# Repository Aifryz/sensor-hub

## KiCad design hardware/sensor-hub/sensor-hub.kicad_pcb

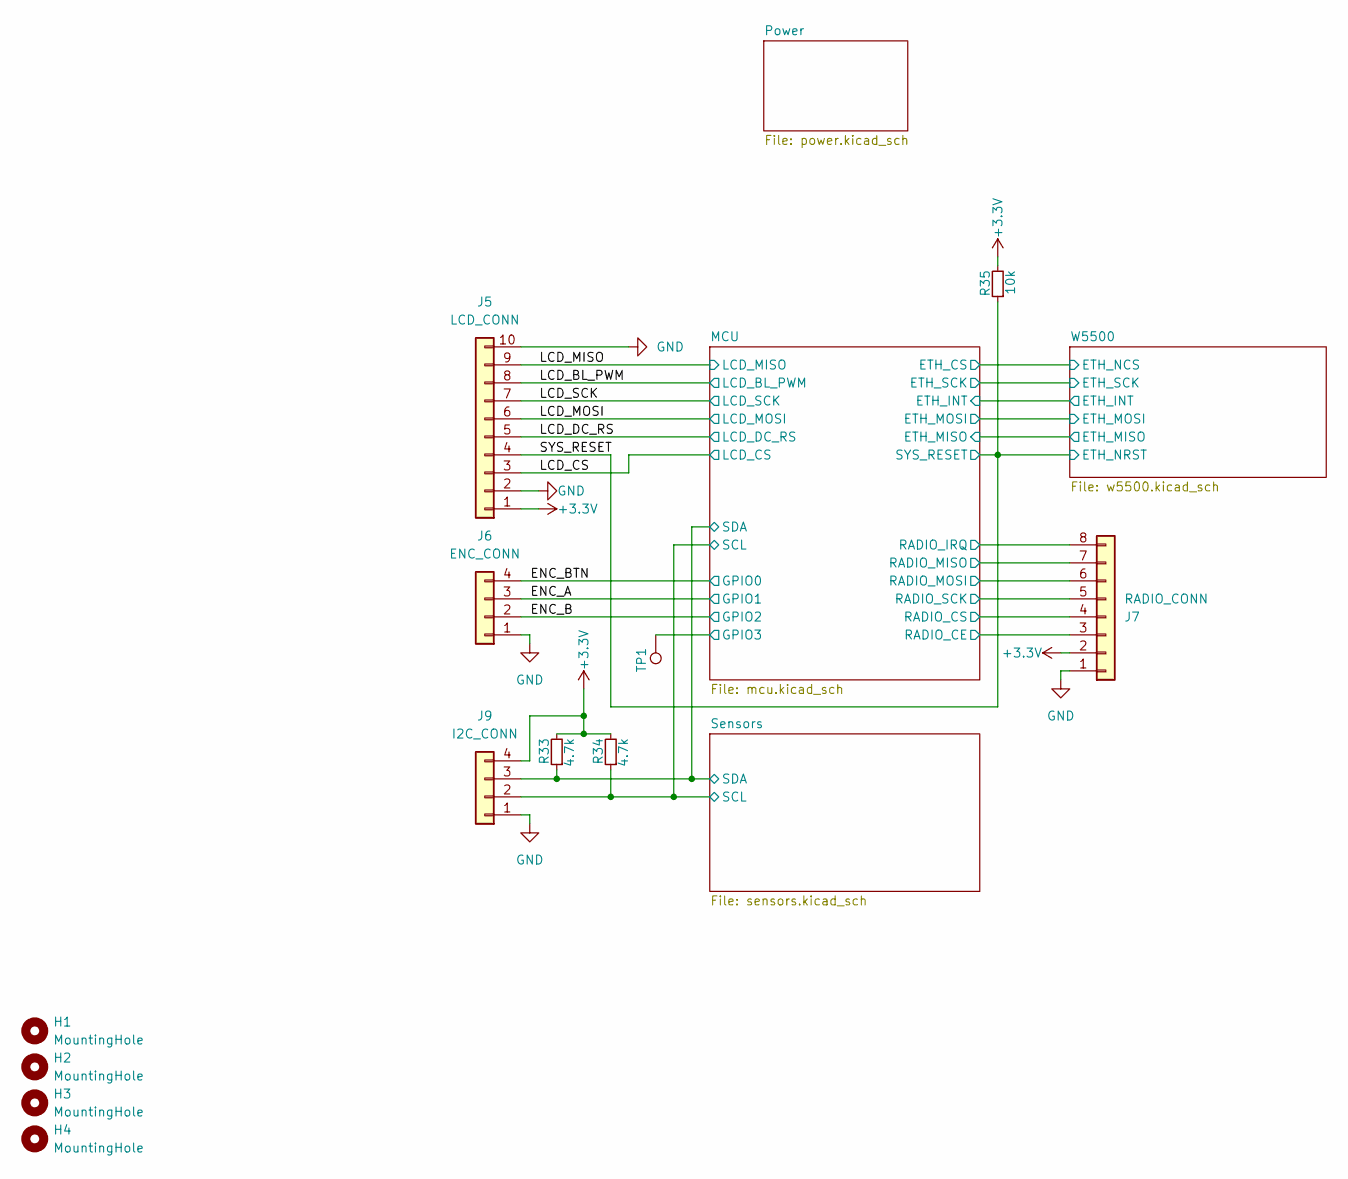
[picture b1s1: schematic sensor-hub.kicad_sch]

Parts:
H1, H2, H3, H4: MountingHole; MountingHole_3mm
J5: LCD_CONN; TE_Micro-MaTch_1-215079-0_2x05_P1.27mm_Vertical
J6: ENC_CONN; TE_Micro-MaTch_215079-4_2x02_P1.27mm_Vertical
J7: RADIO_CONN; TE_Micro-MaTch_215079-8_2x04_P1.27mm_Vertical
J9: I2C_CONN; PinHeader_1x04_P2.54mm_Vertical
R33, R34: 4.7k; R_0603_1608Metric
R35: 10k; R_0603_1608Metric
TP1: TestPoint; TestPoint_Pad_D1.0mm

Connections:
+3.3V: J5.1, J7.2, J9.4, R33.2, R34.2, R35.2; also elsewhere on the board
/ENC_A: J6.3; also elsewhere on the board
/ENC_B: J6.2; also elsewhere on the board
/ENC_BTN: J6.4; also elsewhere on the board
/LCD_BL_PWM: J5.8; also elsewhere on the board
/LCD_CS: J5.3; also elsewhere on the board
/LCD_DC_RS: J5.5; also elsewhere on the board
/LCD_MISO: J5.9; also elsewhere on the board
/LCD_MOSI: J5.6; also elsewhere on the board
/LCD_SCK: J5.7; also elsewhere on the board
/MCU/GPIO3: TP1.1; also elsewhere on the board
/MCU/RADIO_CE: J7.3; also elsewhere on the board
/MCU/RADIO_CS: J7.4; also elsewhere on the board
/MCU/RADIO_IRQ: J7.8; also elsewhere on the board
/MCU/RADIO_MISO: J7.7; also elsewhere on the board
/MCU/RADIO_MOSI: J7.6; also elsewhere on the board
/MCU/RADIO_SCK: J7.5; also elsewhere on the board
/MCU/SCL: J9.2, R34.1; also elsewhere on the board
/MCU/SDA: J9.3, R33.1; also elsewhere on the board
/SYS_RESET: J5.4, R35.1; also elsewhere on the board
GND: J5.2, J5.10, J6.1, J7.1, J9.1; also elsewhere on the board

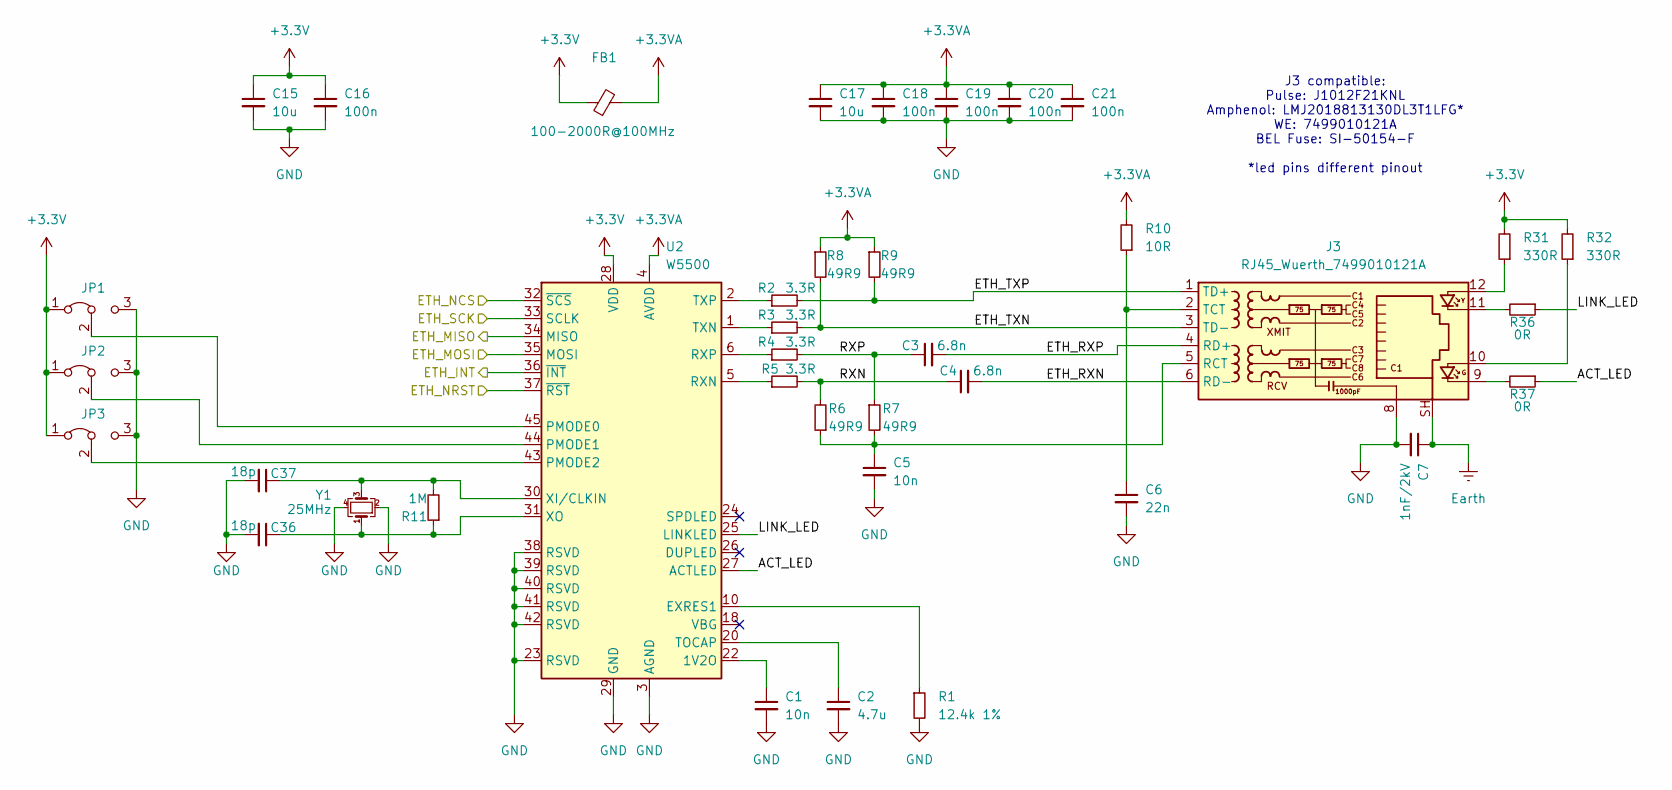
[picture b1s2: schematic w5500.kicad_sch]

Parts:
C1, C5: 10n; C_0603_1608Metric
C2: 4.7u; C_0603_1608Metric
C3, C4: 6.8n; C_0603_1608Metric
C6: 22n; C_0603_1608Metric
C7: 1nF/2kV; C_1206_3216Metric
C15, C17: 10u; C_0805_2012Metric
C16, C18, C19, C20, C21: 100n; C_0603_1608Metric
C36, C37: 18p; C_0603_1608Metric
FB1: 100-2000R@100MHz; L_0603_1608Metric
J3: RJ45_Wuerth_7499010121A; RJ45_Wuerth_7499010121A_Horizontal
JP1, JP2, JP3: SolderJumper-3_P1.3mm_Bridged12_RoundedPad1.0x1.5mm
R1: 12.4k 1%; R_0603_1608Metric
R2, R3, R4, R5: 3.3R; R_0603_1608Metric
R6, R7, R8, R9: 49R9; R_0603_1608Metric
R10: 10R; R_0603_1608Metric
R11: 1M; R_0603_1608Metric
R31, R32: 330R; R_0603_1608Metric
R36, R37: 0R; R_0603_1608Metric
U2: W5500; LQFP-48_7x7mm_P0.5mm
Y1: 25MHz; Crystal_SMD_SeikoEpson_TSX3225-4Pin_3.2x2.5mm

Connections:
+3.3V: C15.1, C16.1, FB1.1, JP1.1 (A), JP2.1 (A), JP3.1 (A), R31.2, R32.2, U2.28 (VDD); also elsewhere on the board
+3.3VA: C17.1, C18.1, C19.1, C20.1, C21.1, FB1.2, R8.1, R9.1, R10.2, U2.4 (AVDD), U2.8 (AVDD), U2.11 (AVDD), U2.15 (AVDD), U2.17 (AVDD), U2.21 (AVDD)
/MCU/ETH_CS: U2.32 (~SCS); also elsewhere on the board
/MCU/ETH_INT: U2.36 (~INT); also elsewhere on the board
/MCU/ETH_MISO: U2.34 (MISO); also elsewhere on the board
/MCU/ETH_MOSI: U2.35 (MOSI); also elsewhere on the board
/MCU/ETH_SCK: U2.33 (SCLK); also elsewhere on the board
/SYS_RESET: U2.37 (~RST); also elsewhere on the board
/W5500/ACT_LED: R37.1, U2.27 (ACTLED)
/W5500/ETH_RXN: C4.2, J3.6 (RD-)
/W5500/ETH_RXP: C3.2, J3.4 (RD+)
/W5500/ETH_TXN: J3.3 (TD-), R3.2, R8.2
/W5500/ETH_TXP: J3.1 (TD+), R2.2, R9.2
/W5500/LINK_LED: R36.1, U2.25 (LINKLED)
/W5500/RXN: C4.1, R5.2, R6.2
/W5500/RXP: C3.1, R4.2, R7.1
Earth: C7.1, J3.SH
GND: C1.2, C2.2, C5.2, C6.2, C7.2, C15.2, C16.2, C17.2, C18.2, C19.2, C20.2, C21.2, C36.2, C37.2, J3.8, JP1.3 (B), JP2.3 (B), JP3.3 (B), R1.2, U2.3 (AGND), U2.9 (AGND), U2.14 (AGND), U2.16 (AGND), U2.19 (AGND), U2.23 (RSVD), U2.29 (GND), U2.38 (RSVD), U2.39 (RSVD), U2.40 (RSVD), U2.41 (RSVD), U2.42 (RSVD), U2.48 (AGND), Y1.2, Y1.4; also elsewhere on the board
unnamed: J3.9, R37.2
unnamed: J3.10, R32.1
unnamed: J3.11, R36.2
unnamed: J3.12, R31.1
unnamed: C5.1, J3.5 (RCT), R6.1, R7.2
unnamed: C6.1, J3.2 (TCT), R10.1
unnamed: JP1.2 (C), U2.45 (PMODE0)
unnamed: JP2.2 (C), U2.44 (PMODE1)
unnamed: JP3.2 (C), U2.43 (PMODE2)
unnamed: C1.1, U2.22 (1V2O)
unnamed: R1.1, U2.10 (EXRES1)
unnamed: R5.1, U2.5 (RXN)
unnamed: R4.1, U2.6 (RXP)
unnamed: C2.1, U2.20 (TOCAP)
unnamed: R3.1, U2.1 (TXN)
unnamed: R2.1, U2.2 (TXP)
unnamed: C37.1, R11.2, U2.30 (XI/CLKIN), Y1.3
unnamed: C36.1, R11.1, U2.31 (XO), Y1.1

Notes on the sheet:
J3 compatible: Pulse: J1012F21KNL Amphenol: LMJ2018813130DL3T1LFG* WE: 7499010121A BEL Fuse: SI-50154-F *led pins different pinout

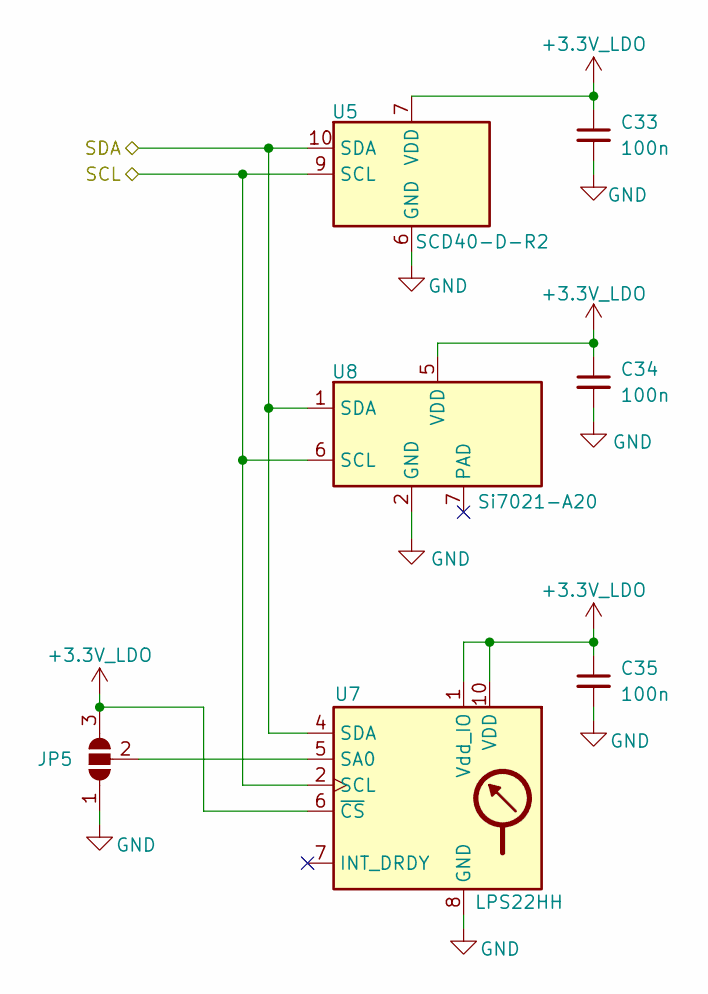
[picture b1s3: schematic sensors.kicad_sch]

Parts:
C33, C34, C35: 100n; C_0603_1608Metric
JP5: SolderJumper_3_Open; SolderJumper-3_P1.3mm_Open_RoundedPad1.0x1.5mm
U5: SCD40-D-R2; Sensirion_SCD4x-1EP_10.1x10.1mm_P1.25mm_EP4.8x4.8mm
U7: LPS22HH; ST_HLGA-10_2x2mm_P0.5mm_LayoutBorder3x2y
U8: Si7021-A20; DFN-6-1EP_3x3mm_P1mm_EP1.5x2.4mm

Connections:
+3.3V_LDO: C33.1, C34.1, C35.1, JP5.3 (B), U5.7 (VDD), U5.19 (VDD), U7.1 (Vdd_IO), U7.6 (~CS), U7.10 (VDD), U8.5 (VDD); also elsewhere on the board
/MCU/SCL: U5.9 (SCL), U7.2 (SCL), U8.6 (SCL); also elsewhere on the board
/MCU/SDA: U5.10 (SDA), U7.4 (SDA), U8.1 (SDA); also elsewhere on the board
GND: C33.2, C34.2, C35.2, JP5.1 (A), U5.6 (GND), U5.20 (GND), U5.21 (GND), U7.3 (GND), U7.8 (GND), U7.9 (GND), U8.2 (GND); also elsewhere on the board
unnamed: JP5.2 (C), U7.5 (SA0)

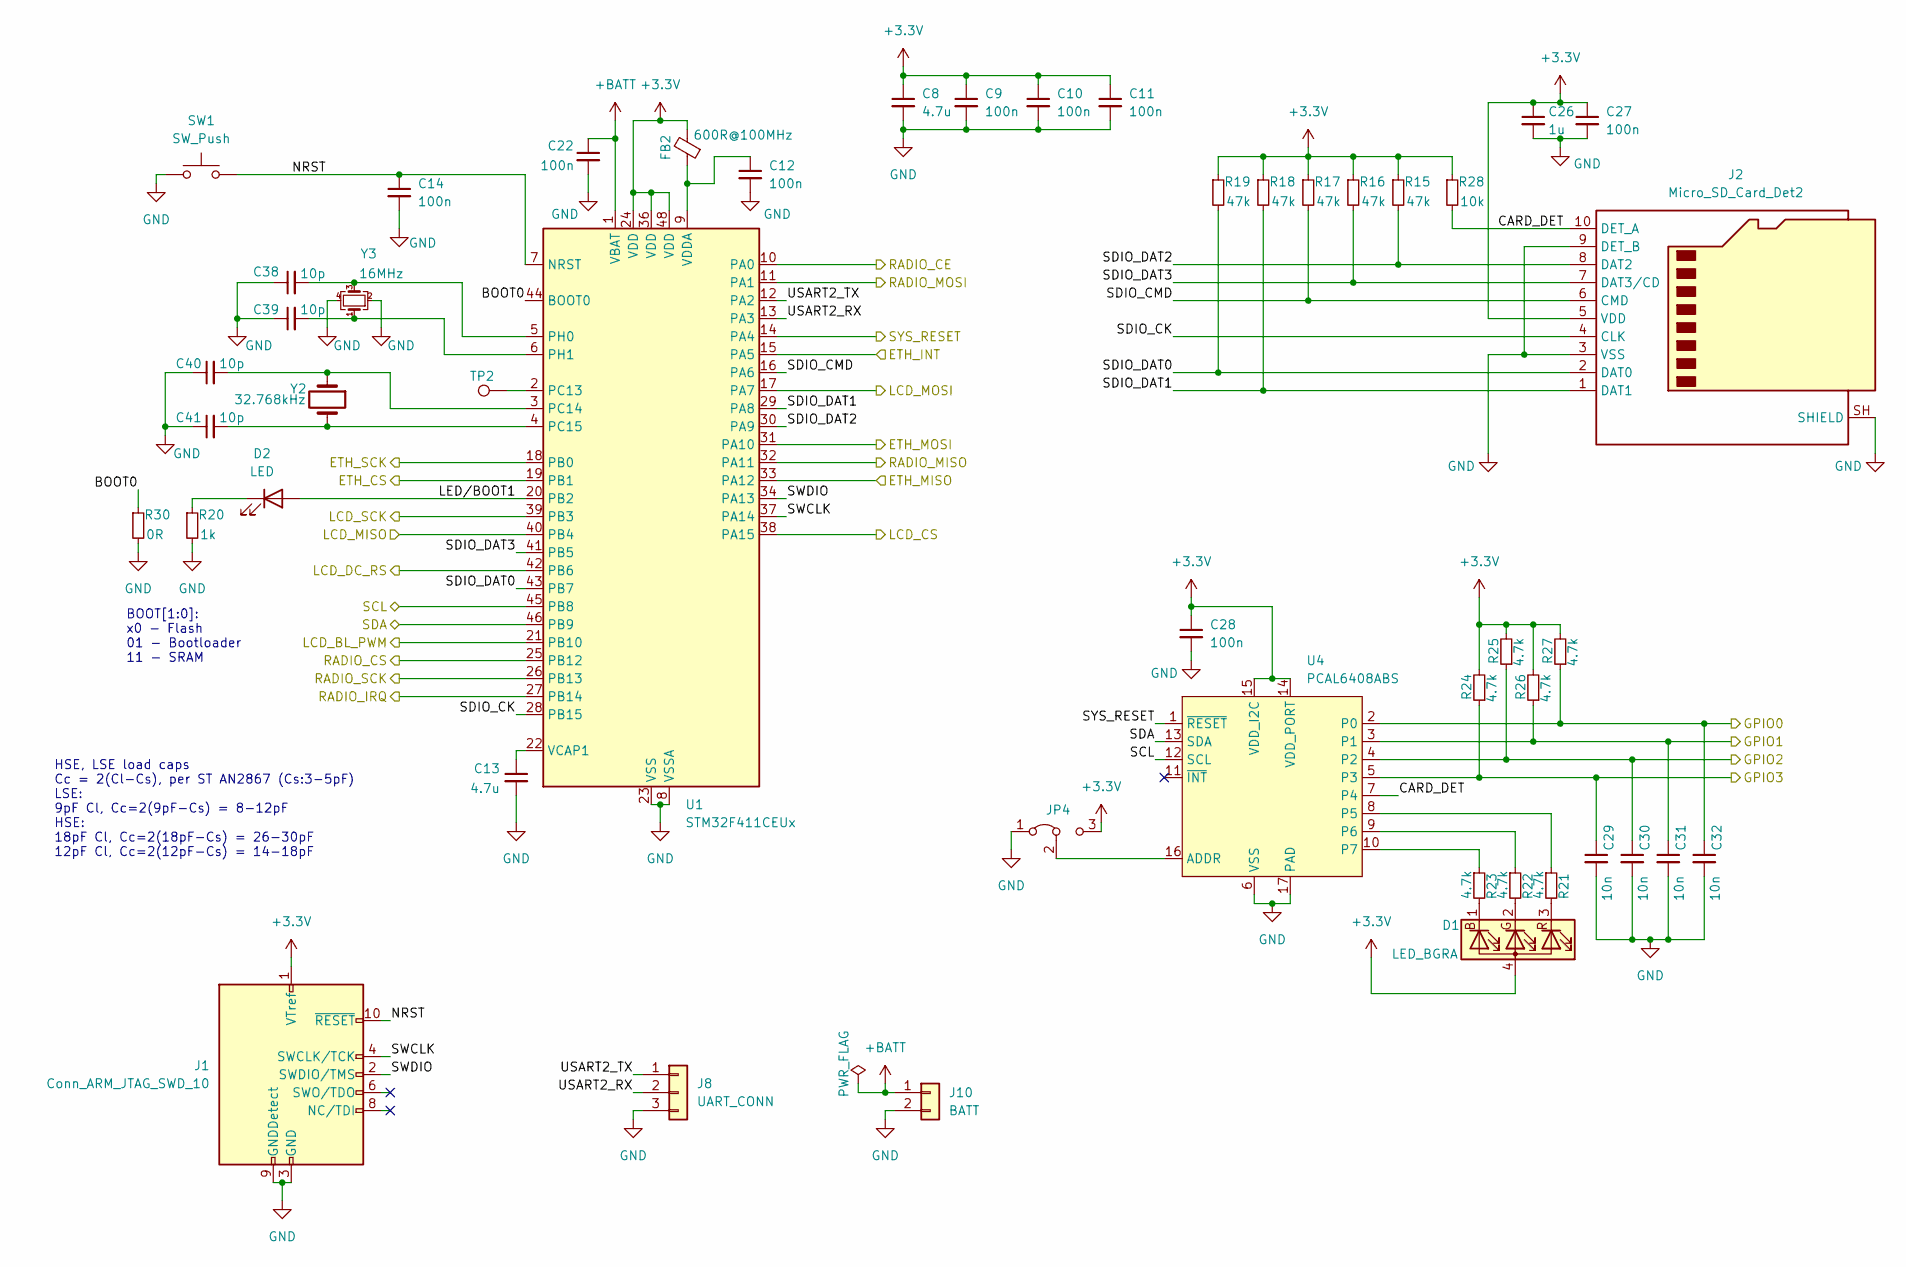
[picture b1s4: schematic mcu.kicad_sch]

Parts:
C8, C13: 4.7u; C_0603_1608Metric
C9, C10, C11, C12, C14, C22, C27, C28: 100n; C_0603_1608Metric
C26: 1u; C_0603_1608Metric
C29, C30, C31, C32: 10n; C_0603_1608Metric
C38, C39, C40, C41: 10p; C_0603_1608Metric
D1: LED_BGRA; LED_Cree-PLCC4_3.2x2.8mm_CCW
D2: LED; LED_0603_1608Metric
FB2: 600R@100MHz; L_0603_1608Metric
J1: Conn_ARM_JTAG_SWD_10; PinHeader_2x05_P1.27mm_Vertical_SMD
J2: Micro_SD_Card_Det2; MicroSD_Det2
J8: UART_CONN; PinHeader_1x03_P2.54mm_Vertical
J10: BATT; BatteryHolder_MYOUNG_BS-07-A1BJ001_CR2032
JP4: SolderJumper-3_P1.3mm_Bridged12_RoundedPad1.0x1.5mm
R15, R16, R17, R18, R19: 47k; R_0603_1608Metric
R20: 1k; R_0603_1608Metric
R21, R22, R23, R24, R25, R26, R27: 4.7k; R_0603_1608Metric
R28: 10k; R_0603_1608Metric
R30: 0R; R_0603_1608Metric
SW1: SW_Push; SW_SPST_CK_RS282G05A3
TP2: TestPoint; TestPoint_Pad_D1.0mm
U1: STM32F411CEUx; QFN-48-1EP_7x7mm_P0.5mm_EP5.6x5.6mm
U4: PCAL6408ABS; QFN-16-1EP_3x3mm_P0.5mm_EP1.45x1.45mm
Y2: 32.768kHz; Crystal_SMD_3215-2Pin_3.2x1.5mm
Y3: 16MHz; Crystal_SMD_SeikoEpson_TSX3225-4Pin_3.2x2.5mm

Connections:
+3.3V: C8.1, C9.1, C10.1, C11.1, C26.1, C27.1, C28.1, D1.4 (A), FB2.2, J1.1 (VTref), J2.5 (VDD), JP4.3 (B), R15.1, R16.1, R17.1, R18.1, R19.1, R24.2, R25.2, R26.2, R27.2, R28.1, U1.24 (VDD), U1.36 (VDD), U1.48 (VDD), U4.14 (VDD_PORT), U4.15 (VDD_I2C); also elsewhere on the board
+BATT: C22.1, J10.1, U1.1 (VBAT)
/ENC_A: C31.1, R26.1, U4.3 (P1); also elsewhere on the board
/ENC_B: C30.1, R25.1, U4.4 (P2); also elsewhere on the board
/ENC_BTN: C32.1, R27.1, U4.2 (P0); also elsewhere on the board
/LCD_BL_PWM: U1.21 (PB10); also elsewhere on the board
/LCD_CS: U1.38 (PA15); also elsewhere on the board
/LCD_DC_RS: U1.42 (PB6); also elsewhere on the board
/LCD_MISO: U1.40 (PB4); also elsewhere on the board
/LCD_MOSI: U1.17 (PA7); also elsewhere on the board
/LCD_SCK: U1.39 (PB3); also elsewhere on the board
/MCU/BOOT0: R30.1, U1.44 (BOOT0)
/MCU/CARD_DET: J2.10 (DET_A), R28.2, U4.7 (P4)
/MCU/ETH_CS: U1.19 (PB1); also elsewhere on the board
/MCU/ETH_INT: U1.15 (PA5); also elsewhere on the board
/MCU/ETH_MISO: U1.33 (PA12); also elsewhere on the board
/MCU/ETH_MOSI: U1.31 (PA10); also elsewhere on the board
/MCU/ETH_SCK: U1.18 (PB0); also elsewhere on the board
/MCU/GPIO3: C29.1, R24.1, U4.5 (P3); also elsewhere on the board
/MCU/LED/BOOT1: D2.2 (A), U1.20 (PB2)
/MCU/NRST: C14.1, J1.10 (~RESET), SW1.2, U1.7 (NRST)
/MCU/RADIO_CE: U1.10 (PA0); also elsewhere on the board
/MCU/RADIO_CS: U1.25 (PB12); also elsewhere on the board
/MCU/RADIO_IRQ: U1.27 (PB14); also elsewhere on the board
/MCU/RADIO_MISO: U1.32 (PA11); also elsewhere on the board
/MCU/RADIO_MOSI: U1.11 (PA1); also elsewhere on the board
/MCU/RADIO_SCK: U1.26 (PB13); also elsewhere on the board
/MCU/SCL: U1.45 (PB8), U4.12 (SCL); also elsewhere on the board
/MCU/SDA: U1.46 (PB9), U4.13 (SDA); also elsewhere on the board
/MCU/SDIO_CK: J2.4 (CLK), U1.28 (PB15)
/MCU/SDIO_CMD: J2.6 (CMD), R17.2, U1.16 (PA6)
/MCU/SDIO_DAT0: J2.2 (DAT0), R19.2, U1.43 (PB7)
/MCU/SDIO_DAT1: J2.1 (DAT1), R18.2, U1.29 (PA8)
/MCU/SDIO_DAT2: J2.8 (DAT2), R15.2, U1.30 (PA9)
/MCU/SDIO_DAT3: J2.7 (DAT3/CD), R16.2, U1.41 (PB5)
/MCU/SWCLK: J1.4 (SWCLK/TCK), U1.37 (PA14)
/MCU/SWDIO: J1.2 (SWDIO/TMS), U1.34 (PA13)
/MCU/USART2_RX: J8.2, U1.13 (PA3)
/MCU/USART2_TX: J8.1, U1.12 (PA2)
/SYS_RESET: U1.14 (PA4), U4.1 (~RESET); also elsewhere on the board
GND: C8.2, C9.2, C10.2, C11.2, C12.2, C13.2, C14.2, C22.2, C26.2, C27.2, C28.2, C29.2, C30.2, C31.2, C32.2, C38.1, C39.1, C40.1, C41.1, J1.3 (GND), J1.5 (GND), J1.9 (GNDDetect), J2.3 (VSS), J2.9 (DET_B), J2.SH (SHIELD), J8.3, J10.2, JP4.1 (A), R20.2, R30.2, SW1.1, U1.8 (VSSA), U1.23 (VSS), U1.35 (VSS), U1.47 (VSS), U1.49 (VSS), U4.6 (VSS), U4.17 (PAD), Y3.2, Y3.4; also elsewhere on the board
unnamed: D1.1 (BK), R23.2
unnamed: D1.2 (GK), R22.2
unnamed: D1.3 (RK), R21.2
unnamed: D2.1 (K), R20.1
unnamed: JP4.2 (C), U4.16 (ADDR)
unnamed: TP2.1, U1.2 (PC13)
unnamed: C40.2, U1.3 (PC14), Y2.1
unnamed: C41.2, U1.4 (PC15), Y2.2
unnamed: C38.2, U1.5 (PH0), Y3.3
unnamed: C39.2, U1.6 (PH1), Y3.1
unnamed: C13.1, U1.22 (VCAP1)
unnamed: C12.1, FB2.1, U1.9 (VDDA)
unnamed: R21.1, U4.8 (P5)
unnamed: R22.1, U4.9 (P6)
unnamed: R23.1, U4.10 (P7)

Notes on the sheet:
BOOT[1:0]: x0 - Flash 01 - Bootloader 11 - SRAM
HSE, LSE load caps Cc = 2(Cl-Cs), per ST AN2867 (Cs:3-5pF) LSE: 9pF Cl, Cc=2(9pF-Cs) = 8-12pF HSE: 18pF Cl, Cc=2(18pF-Cs) = 26-30pF 12pF Cl, Cc=2(12pF-Cs) = 14-18pF

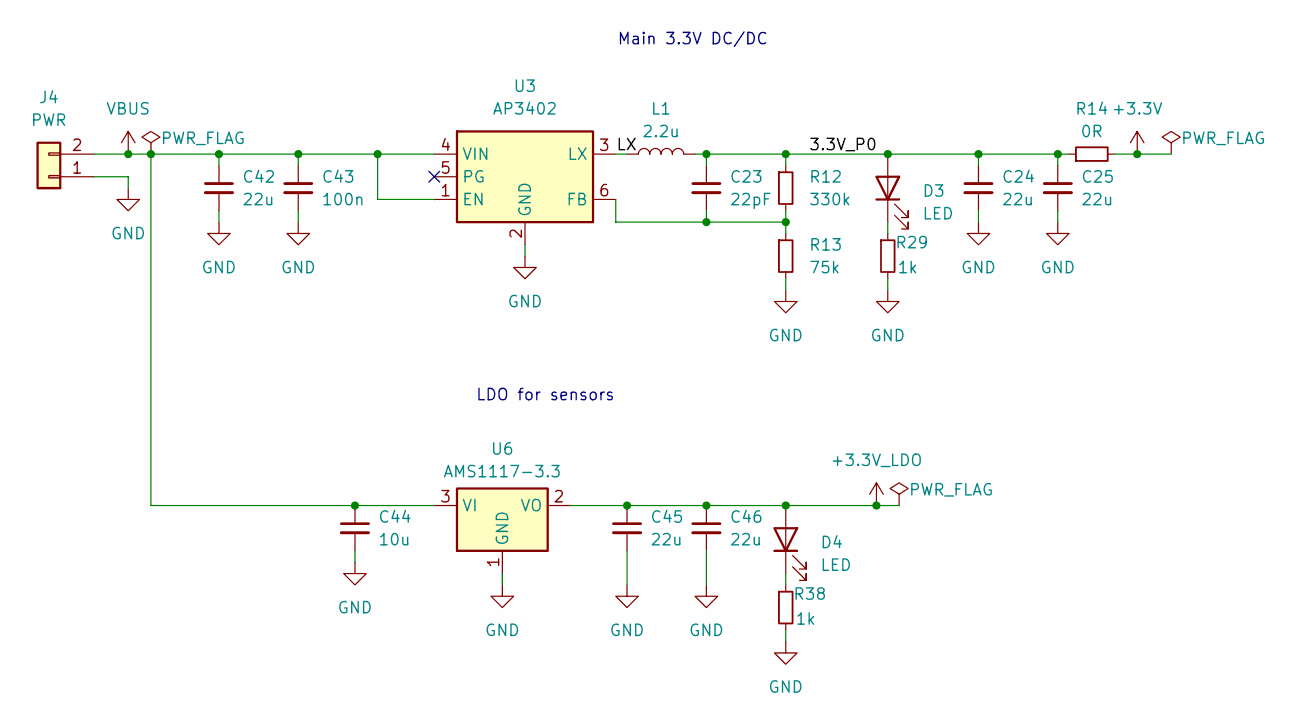
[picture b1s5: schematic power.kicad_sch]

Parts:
C23: 22pF; C_0603_1608Metric
C24, C25, C42, C45, C46: 22u; C_0805_2012Metric
C43: 100n; C_0603_1608Metric
C44: 10u; C_0805_2012Metric
D3, D4: LED; LED_0603_1608Metric
J4: PWR; PinHeader_1x02_P2.54mm_Vertical
L1: 2.2u; L_APV_ANR5045
R12: 330k; R_0603_1608Metric
R13: 75k; R_0603_1608Metric
R14: 0R; R_0603_1608Metric
R29, R38: 1k; R_0603_1608Metric
U3: AP3402; TSOT-23-6
U6: AMS1117-3.3; SOT-223-3_TabPin2

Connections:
+3.3V: R14.2; also elsewhere on the board
+3.3V_LDO: C45.1, C46.1, D4.2 (A), U6.2 (VO); also elsewhere on the board
/Power/3.3V_P0: C23.1, C24.1, C25.1, D3.2 (A), L1.2, R12.1, R14.1
/Power/LX: L1.1, U3.3 (LX)
GND: C24.2, C25.2, C42.2, C43.2, C44.2, C45.2, C46.2, J4.1, R13.2, R29.2, R38.2, U3.2 (GND), U6.1 (GND); also elsewhere on the board
unnamed: D3.1 (K), R29.1
unnamed: D4.1 (K), R38.1
unnamed: C23.2, R12.2, R13.1, U3.6 (FB)
VBUS: C42.1, C43.1, C44.1, J4.2, U3.1 (EN), U3.4 (VIN), U6.3 (VI)

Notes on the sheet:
LDO for sensors
Main 3.3V DC/DC

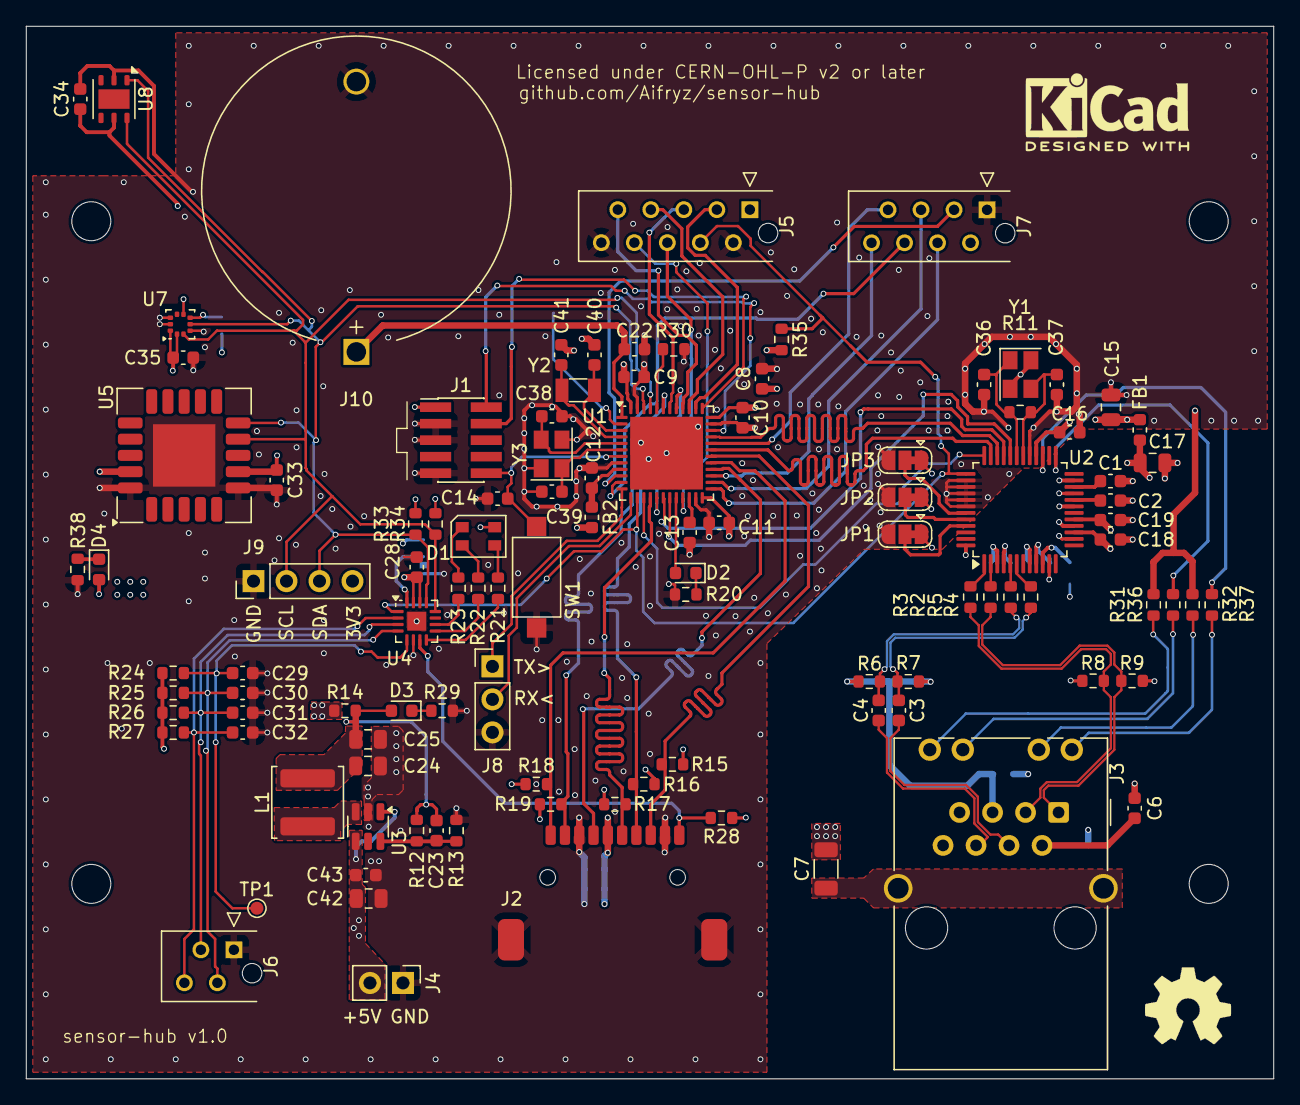
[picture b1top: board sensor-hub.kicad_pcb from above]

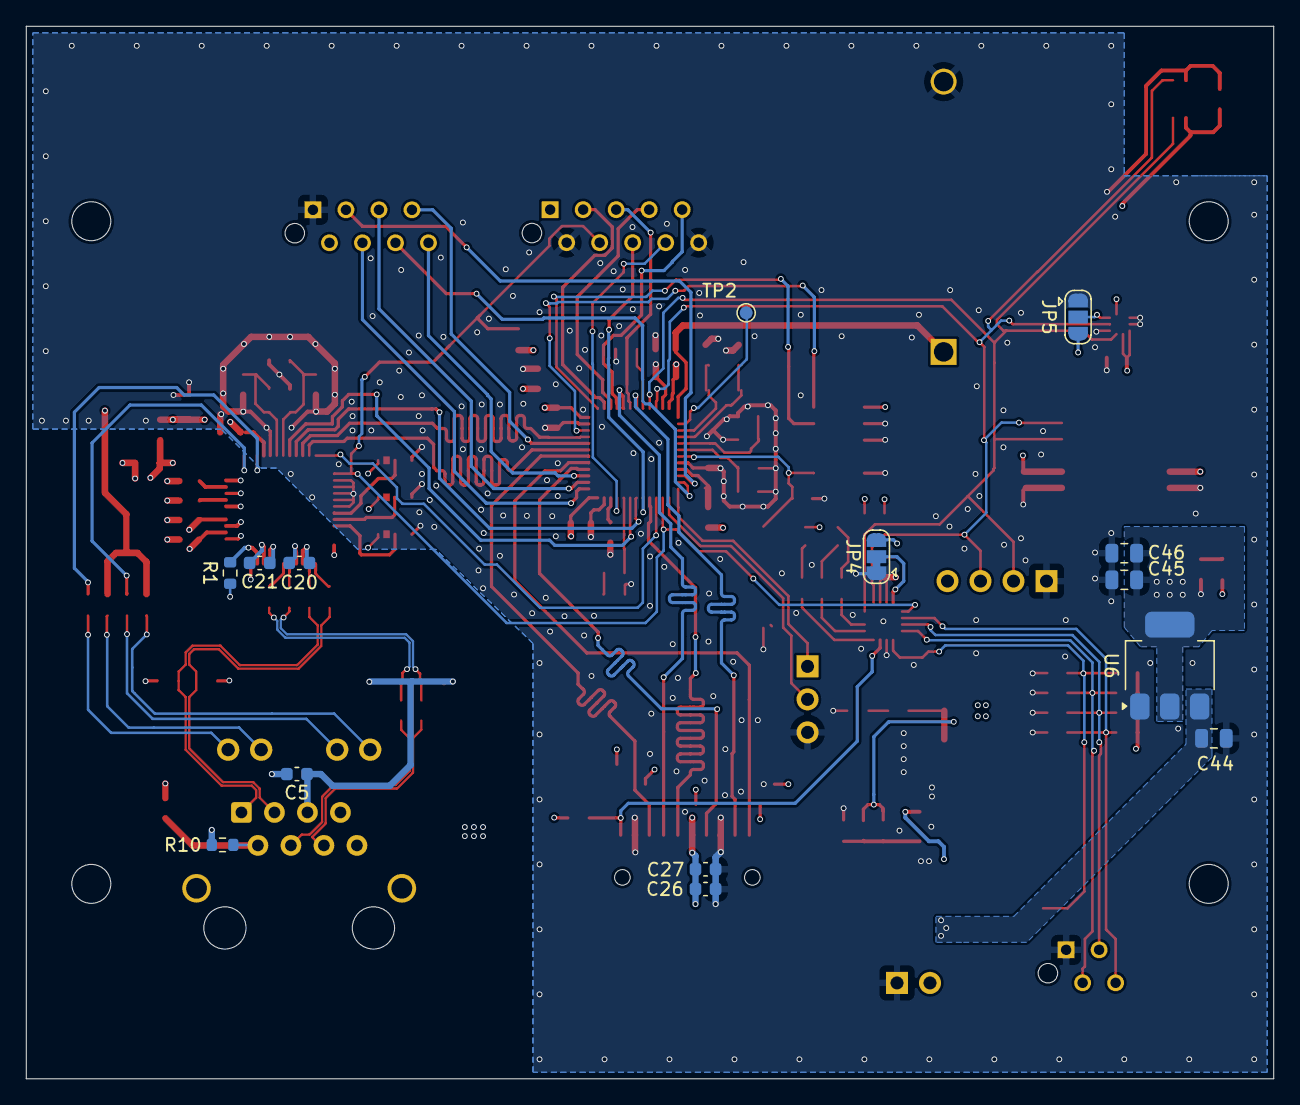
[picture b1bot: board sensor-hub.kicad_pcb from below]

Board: 4 copper layers, 96.0 x 81.0 mm, 124 parts (14 on the bottom side), 92 nets.

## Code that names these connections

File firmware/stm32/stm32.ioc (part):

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Mcu.Name=STM32F411C(C-E)Ux
Mcu.Package=UFQFPN48
Mcu.UserName=STM32F411CEUx
PA0-WKUP.GPIOParameters=GPIO_Label
PA0-WKUP.GPIO_Label=RADIO_CE
PA0-WKUP.Signal=GPIO_Output
PA1.GPIOParameters=GPIO_Label
PA1.GPIO_Label=RADIO_MOSI
PA1.Mode=Full_Duplex_Master
PA1.Signal=SPI4_MOSI
PA10.GPIOParameters=GPIO_Label
PA10.GPIO_Label=ETH_MOSI
PA10.Mode=Full_Duplex_Master
PA10.Signal=SPI5_MOSI
PA11.GPIOParameters=GPIO_Label
PA11.GPIO_Label=RADIO_MISO
PA11.Mode=Full_Duplex_Master
PA11.Signal=SPI4_MISO
PA12.GPIOParameters=GPIO_Label
PA12.GPIO_Label=ETH_MISO
PA12.Mode=Full_Duplex_Master
PA12.Signal=SPI5_MISO
PA13.Mode=Serial_Wire
PA13.Signal=SYS_JTMS-SWDIO
PA14.Mode=Serial_Wire
PA14.Signal=SYS_JTCK-SWCLK
PA15.GPIOParameters=GPIO_Label
PA15.GPIO_Label=LCD_CS
PA15.Signal=GPIO_Output
PA2.Mode=Asynchronous
PA2.Signal=USART2_TX
PA3.Mode=Asynchronous
PA3.Signal=USART2_RX
PA4.GPIOParameters=GPIO_Label
PA4.GPIO_Label=SYS_RESET
PA4.Signal=GPIO_Output
PA5.GPIOParameters=GPIO_Label
PA5.GPIO_Label=ETH_INT
PA5.Signal=GPXTI5
PA6.Mode=SD_4_bits_Wide_bus
PA6.Signal=SDIO_CMD
PA7.GPIOParameters=GPIO_Label
PA7.GPIO_Label=LCD_MOSI
PA7.Mode=Full_Duplex_Master
PA7.Signal=SPI1_MOSI
PA8.Mode=SD_4_bits_Wide_bus
PA8.Signal=SDIO_D1
PA9.Mode=SD_4_bits_Wide_bus
PA9.Signal=SDIO_D2
PB0.GPIOParameters=GPIO_Label
PB0.GPIO_Label=ETH_SCK
PB0.Mode=Full_Duplex_Master
PB0.Signal=SPI5_SCK
PB1.GPIOParameters=GPIO_Label
PB1.GPIO_Label=ETH_CS
PB1.Signal=GPIO_Output
PB10.GPIOParameters=GPIO_Label
PB10.GPIO_Label=LCD_BL_PWM
PB10.Signal=S_TIM2_CH3
PB12.GPIOParameters=GPIO_Label
PB12.GPIO_Label=RADIO_CS
PB12.Signal=GPIO_Output
PB13.GPIOParameters=GPIO_Label
PB13.GPIO_Label=RADIO_SCK
PB13.Mode=Full_Duplex_Master
PB13.Signal=SPI4_SCK
PB14.GPIOParameters=GPIO_Label
PB14.GPIO_Label=RADIO_IRQ
PB14.Signal=GPXTI14
PB15.Mode=SD_4_bits_Wide_bus
PB15.Signal=SDIO_CK
PB2.GPIOParameters=GPIO_Label
PB2.GPIO_Label=SYS_LED
PB2.Signal=GPIO_Output
PB3.GPIOParameters=GPIO_Label
PB3.GPIO_Label=LCD_SCK
PB3.Mode=Full_Duplex_Master
PB3.Signal=SPI1_SCK
PB4.GPIOParameters=GPIO_Label
PB4.GPIO_Label=LCD_MISO
PB4.Mode=Full_Duplex_Master
PB4.Signal=SPI1_MISO
PB5.Mode=SD_4_bits_Wide_bus
PB5.Signal=SDIO_D3
PB6.GPIOParameters=GPIO_Label
PB6.GPIO_Label=LCD_DC_RS
PB6.Signal=GPIO_Output
PB7.Mode=SD_4_bits_Wide_bus
PB7.Signal=SDIO_D0
PB8.Mode=I2C
PB8.Signal=I2C1_SCL
PB9.Mode=I2C
PB9.Signal=I2C1_SDA
PC14-OSC32_IN.Mode=LSE-External-Oscillator
PC14-OSC32_IN.Signal=RCC_OSC32_IN
PC15-OSC32_OUT.Mode=LSE-External-Oscillator
PC15-OSC32_OUT.Signal=RCC_OSC32_OUT
PH0\ -\ OSC_IN.Mode=HSE-External-Oscillator
PH0\ -\ OSC_IN.Signal=RCC_OSC_IN
PH1\ -\ OSC_OUT.Mode=HSE-External-Oscillator
PH1\ -\ OSC_OUT.Signal=RCC_OSC_OUT
RCC.HSE_VALUE=16000000
RCC.SYSCLKFreq_VALUE=100000000
RCC.SYSCLKSource=RCC_SYSCLKSOURCE_PLLCLK
board=custom

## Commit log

2022-12-04 Initial config, add stm32 project
2023-02-04 Add peripherals
2023-02-11 Add FreeRTOS, LVGL
2023-02-28 Fix config, add newlib threadsafe, add logging stub
2023-04-03 Add more partial logging
2023-04-05 Add parts of nrf radio, some gpio handling
2023-04-10 Add board gpio
2023-04-29 Add some NRF24 regs
2023-07-16 Add safebits, reorganize sources
2023-07-16 Fix lv config
2025-03-08 Add initial sensor-hub schematic
2025-03-08 Add MicroSD card footprint
2025-03-15 Add sensors, connectors
2025-03-27 Change crystal packages, assign footprints
2025-04-19 Assign remaining footprints, change HT sensor
2025-04-29 Start layout
2025-05-05 Restart layout with proper constraints
2025-05-10 Core layout done
2025-05-10 Most layout done
2025-05-13 Layout
2025-05-17 DRC fixes
2025-05-17 Finalize layout
2025-05-18 V1.0
    Fixed value typos, replaced vias with 0.3/0.45, added production files
2025-06-26 Restarted firmware project
2025-07-08 Fixup
2025-10-05 Temporary work for nrf24
2025-10-06 Initialize LCD
2025-10-07 Reorganize files
2026-02-08 Add LVGL screen driver
2026-02-08 LCD cleanup
2026-02-08 Rotate screen display
2026-02-15 Initial data readout
2026-02-15 Cleanup, remove redundant prints
2026-02-16 Add status logs
2026-02-23 nrf24 radio working
2026-02-23 Temporary PCAL driver
2026-03-09 Encoder driver
2026-03-09 Fix encoder readout
2026-03-09 PWM LCD backlight
2026-03-12 Refactor LCD driver
2026-05-10 Reorganize some files
2026-05-12 Add i2c driver to support later irq driven approach
2026-05-15 Fix extra reset
2026-05-15 Update to newer firmware pack
    Bump SPI to ~6mb/s
2026-05-31 Logging rework
2026-06-04 Add logging tests
2026-06-05 More tests
2026-06-09 Start logging format refactor
2026-06-18 Add linear stream buffer
2026-06-20 Rename to fifo message buffer
2026-06-20 Add more tests
2026-06-22 Optimize message length a bit
2026-06-30 Add better logging

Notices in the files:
hardware/sensor-hub/sensor-hub.kicad_pcb:
Licensed under CERN-OHL-P v2 or later
